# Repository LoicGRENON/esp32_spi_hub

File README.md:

SPI HUB for ESP32
=================
This repository contains the firmware source code and the hardware design
files.

The design is a fork of the ESP32 Brick from Tinkerforge : https://github.com/Tinkerforge/esp32-brick & https://www.tinkerforge.com/en/doc/Hardware/Bricks/ESP32_Brick.html

It is modified mainly to use "basic parts" components from JLCPCB for cost-effective assembly and also to use a ESP32 with external antenna (ESP32-WROOM-32UE-N16).

Hardware
--------

The hardware is designed with the open source EDA Suite KiCad 6.0 (http://www.kicad.org) and Kikit (https://github.com/yaqwsx/KiKit) is used to generate the assembly files.

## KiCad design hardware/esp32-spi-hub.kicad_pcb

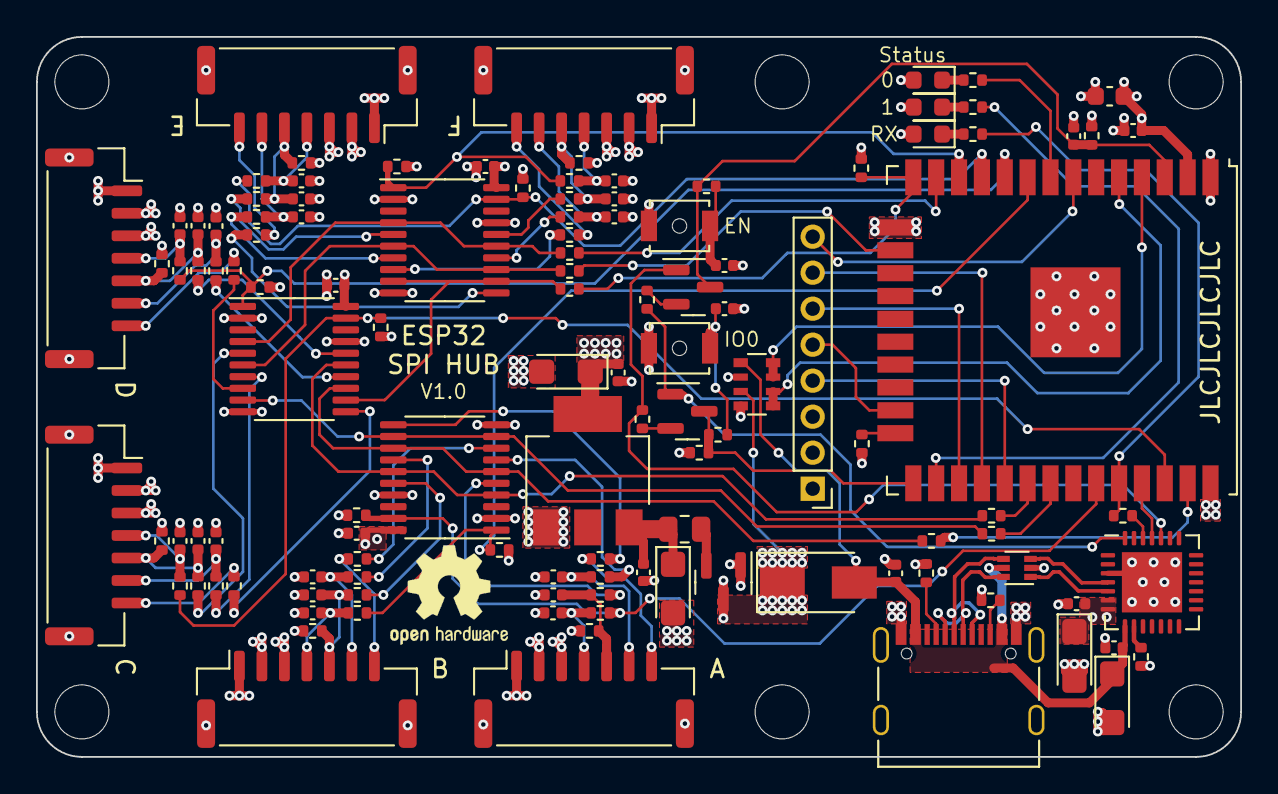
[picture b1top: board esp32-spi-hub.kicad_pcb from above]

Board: 4 copper layers, 66.9 x 40.0 mm, 124 parts (0 on the bottom side), 97 nets.

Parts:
C1, C3, C5, C7, C10, C12, C15, C22, C29: 0.1uF; C_0402_1005Metric
C2, C4, C8, C11: 10uF; CP_EIA-3216-18_Kemet-A
C6: 22uF; C_0603_1608Metric
C9: 10uF; C_0402_1005Metric
C13, C14: 1nF; C_0402_1005Metric
C16, C17, C18, C19, C20, C21, C23, C24, C25, C26, C27, C28, C30, C31, C32, C33, C34, C35: 220pF; C_0402_1005Metric
D1: SS34; D_SMA
D2: YE; LED_0603_1608Metric
D3: GN; LED_0603_1608Metric
D4: BU; LED_0603_1608Metric
FB1: 100 @ 100MHz; R_0805_2012Metric
H1, H2, H3, H4, H5, H6: MountingHole; MountingHole_3mm
J1: EXT_HEADER; PinHeader_1x08_P2.00mm_Vertical
J2, J3, J4, J5, J6, J7: SM07B-GHS-TB; JST_GH_SM07B-GHS-TB_1x07-1MP_P1.25mm_Horizontal
P1: USB_C_Plug_USB2.0; USB_C_Receptacle_Palconn_UTC16-G
Q1: AO3401A; SOT-23
Q2, Q3: S8050; SOT-23
R1: 4.7k; R_0402_1005Metric
R2, R9, R10, R11, R12, R13, R14, R23, R24, R25, R26, R30, R31, R32, R33, R35, R36, R37, R38, R42, R43, R44, R45, R47, R48, R49, R50, R54, R55, R56, R57: 100; R_0402_1005Metric
R3, R4, R5, R6: 12k; R_0402_1005Metric
R7, R8: DNP; R_0402_1005Metric
R15, R16: 5.1k; R_0402_1005Metric
R17, R21: 470; R_0402_1005Metric
R18, R19, R20: 1k; R_0402_1005Metric
R22, R27, R34, R39, R46, R51: 100k; R_0402_1005Metric
R28, R29, R40, R41, R52, R53: 10k; R_0402_1005Metric
RN1: 1k; R_Array_Convex_4x0603
SW1, SW2: SW_Push; SW_SPST_B3U-1000P-B
U1: AMS1117-3.3; SOT-223-3_TabPin2
U2: CP2102-GMR; QFN-28-1EP_5x5mm_P0.5mm_EP3.35x3.35mm
U3: ESP32-WROOM-32UE-N16; ESP32-WROOM-32U
U4: 82400152; SOT-563
U5, U6, U7: 74HC244; TSSOP-20_4.4x6.5mm_P0.65mm

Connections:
5V_USB: C10.1, C11.1, C12.1, D1.2 (A), P1.A4 (VBUS), P1.A9 (VBUS), P1.B4 (VBUS), P1.B9 (VBUS), RN1.5 (R4.2), U2.8 (VBUS), U4.5 (VBUS)
+3V3: C3.1, C4.1, C5.1, C6.1, C7.1, C8.1, C15.1, C22.1, C29.1, D2.2 (A), D3.2 (A), D4.2 (A), J1.3, J2.3, J3.3, J4.3, J5.3, J6.3, J7.3, R1.1, R3.1, R6.1, R22.1, R27.1, R28.1, R29.1, R34.1, R39.1, R40.1, R41.1, R46.1, R51.1, R52.1, R53.1, U1.2 (VO), U2.6 (VDD), U2.7 (VREGIN), U3.2 (VDD), U5.20 (VCC), U6.20 (VCC), U7.20 (VCC)
+5V: D1.1 (K), J1.1, J2.1, J3.1, J4.1, J5.1, J6.1, J7.1, Q1.3 (D), RN1.7 (R2.2)
/IO12: R8.1, R9.1, U3.14 (IO12)
/IO13: R10.1, U3.16 (IO13)
/IO14: R11.1, U3.13 (IO14)
/IO18: R12.1, U3.30 (IO18)
/IO19: R13.1, U3.31 (IO19)
/IO23: R14.1, U3.37 (IO23)
/SPI ports A & B/S1_CLK: R24.1, U5.16 (1Y1)
/SPI ports A & B/S1_MISO: R26.1, U5.8 (1A3)
/SPI ports A & B/S1_MOSI: R25.1, U5.14 (1Y2)
/SPI ports A & B/S2_CLK: R31.1, U5.5 (2Y1)
/SPI ports A & B/S2_MISO: R33.1, U5.11 (2A3)
/SPI ports A & B/S2_MOSI: R32.1, U5.7 (2Y2)
/SPI ports C & D/S1_CLK: R36.1, U6.16 (1Y1)
/SPI ports C & D/S1_MISO: R38.1, U6.8 (1A3)
/SPI ports C & D/S1_MOSI: R37.1, U6.14 (1Y2)
/SPI ports C & D/S2_CLK: R43.1, U6.5 (2Y1)
/SPI ports C & D/S2_MISO: R45.1, U6.11 (2A3)
/SPI ports C & D/S2_MOSI: R44.1, U6.7 (2Y2)
/SPI ports E & F/S1_CLK: R48.1, U7.16 (1Y1)
/SPI ports E & F/S1_MISO: R50.1, U7.8 (1A3)
/SPI ports E & F/S1_MOSI: R49.1, U7.14 (1Y2)
/SPI ports E & F/S2_CLK: R55.1, U7.5 (2Y1)
/SPI ports E & F/S2_MISO: R57.1, U7.11 (2A3)
/SPI ports E & F/S2_MOSI: R56.1, U7.7 (2Y2)
B0-CLK: R11.2, U6.4 (1A1), U7.4 (1A1), U7.15 (2A1)
B0-MISO: R9.2, U6.12 (1Y3), U7.9 (2Y3), U7.12 (1Y3)
B0-MOSI: R10.2, U6.6 (1A2), U7.6 (1A2), U7.13 (2A2)
B0_CS0: R47.1, R53.2, U3.12 (IO27), U7.1 (1OE)
B0_CS1: R52.2, R54.1, U3.11 (IO26), U7.19 (2OE)
B0_CS2: R35.1, R41.2, U3.10 (IO25), U6.1 (1OE)
B1-CLK: R12.2, U5.4 (1A1), U5.15 (2A1), U6.15 (2A1)
B1-MISO: R13.2, U5.9 (2Y3), U5.12 (1Y3), U6.9 (2Y3)
B1-MOSI: R14.2, U5.6 (1A2), U5.13 (2A2), U6.13 (2A2)
B1_CS0: R40.2, R42.1, U3.36 (IO22), U6.19 (2OE)
B1_CS1: R23.1, R29.2, U3.9 (IO33), U5.1 (1OE)
B1_CS2: R28.2, R30.1, U3.33 (IO21), U5.19 (2OE)
ESP_EN: C9.1, Q2.3 (C), R3.2, R17.2, U3.3 (EN)
ESP_IO0: Q3.3 (C), R6.2, R21.2, U3.25 (IO0)
ESP_IO2: R7.1, U3.24 (IO2)
ESP_IO5: J1.4, U3.29 (IO5)
ESP_IO15: J1.5, U3.23 (IO15)
ESP_IO16: J1.6, U3.27 (IO16)
ESP_IO17: J1.7, U3.28 (IO17)
ESP_IO35: J1.8, U3.7 (IO35)
ESP_RXD: R2.2, R18.2, U3.34 (RXD0/IO3)
ESP_TXD: U2.25 (RXD), U3.35 (TXD0/IO1)
GND: C1.2, C2.2, C3.2, C4.2, C5.2, C6.2, C7.2, C8.2, C9.2, C10.2, C11.2, C12.2, C13.2, C14.2, C15.2, C16.2, C17.2, C18.2, C19.2, C20.2, C21.2, C22.2, C23.2, C24.2, C25.2, C26.2, C27.2, C28.2, C29.2, C30.2, C31.2, C32.2, C33.2, C34.2, C35.2, J1.2, J2.2, J2.MP (MountPin), J3.2, J3.MP (MountPin), J4.2, J4.MP (MountPin), J5.2, J5.MP (MountPin), J6.2, J6.MP (MountPin), J7.2, J7.MP (MountPin), P1.A1 (GND), P1.A12 (GND), P1.B1 (GND), P1.B12 (GND), Q1.1 (G), R7.2, R8.2, R15.2, R16.2, RN1.6 (R3.2), RN1.8 (R1.2), SW1.1, SW2.1, U1.1 (GND), U2.3 (GND), U2.29 (GND), U3.1 (GND), U3.15 (GND), U3.38 (GND), U3.39 (GND), U4.2 (GND), U5.2 (1A0), U5.10 (GND), U5.17 (2A0), U6.2 (1A0), U6.10 (GND), U6.17 (2A0), U7.2 (1A0), U7.10 (GND), U7.17 (2A0)
LED_BLUE: R20.2, U3.8 (IO32)
LED_GREEN: R19.2, U3.26 (IO4)
unnamed: C1.1, C2.1, FB1.2, U1.3 (VI)
unnamed: C13.1, R17.1, SW1.2
unnamed: C14.1, R21.1, SW2.2
unnamed: C16.1, J2.4, R23.2
unnamed: C17.1, J2.5, R22.2, R24.2
unnamed: C18.1, J2.6, R25.2
unnamed: C19.1, J3.4, R30.2
unnamed: C20.1, J3.5, R27.2, R31.2
unnamed: C21.1, J3.6, R32.2
unnamed: C23.1, J4.4, R35.2
unnamed: C24.1, J4.5, R34.2, R36.2
unnamed: C25.1, J4.6, R37.2
unnamed: C26.1, J5.4, R42.2
unnamed: C27.1, J5.5, R39.2, R43.2
unnamed: C28.1, J5.6, R44.2
unnamed: C30.1, J6.4, R47.2
unnamed: C31.1, J6.5, R46.2, R48.2
unnamed: C32.1, J6.6, R49.2
unnamed: C33.1, J7.4, R54.2
unnamed: C34.1, J7.5, R51.2, R55.2
unnamed: C35.1, J7.6, R56.2
unnamed: D2.1 (K), R18.1
unnamed: D3.1 (K), R19.1
unnamed: D4.1 (K), R20.1
unnamed: FB1.1, Q1.2 (S)
unnamed: J2.7, R26.2
unnamed: J3.7, R33.2
unnamed: J4.7, R38.2
unnamed: J5.7, R45.2
unnamed: J6.7, R50.2
unnamed: J7.7, R57.2
unnamed: P1.A5 (CC), R15.1
unnamed: P1.B5 (VCONN), R16.1
unnamed: Q2.1 (E), R5.1, U2.24 (~RTS)
unnamed: Q2.2 (B), R4.2
unnamed: Q3.1 (E), R4.1, U2.28 (~DTR)
unnamed: Q3.2 (B), R5.2
unnamed: R1.2, U2.9 (~RST)
unnamed: R2.1, U2.26 (TXD)
unnamed: RN1.1 (R1.1), RN1.2 (R2.1), U3.5 (SENSOR_VN)
unnamed: RN1.3 (R3.1), RN1.4 (R4.1), U3.4 (SENSOR_VP)
USB_CONN_D+: P1.A6 (D+), P1.B6 (D+), U4.4 (I/O2)
USB_CONN_D-: P1.A7 (D-), P1.B7 (D-), U4.6 (I/O1)
USB_D+: U2.4 (D+), U4.3 (I/O2)
USB_D-: U2.5 (D-), U4.1 (I/O1)

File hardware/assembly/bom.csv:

Comment,Designator,Footprint,LCSC
0.1uF,"C1,C3,C5,C7,C10,C12,C15,C22,C29",Capacitor_SMD:C_0402_1005Metric,C1525
10uF,"C2,C4,C8,C11",Capacitor_Tantalum_SMD:CP_EIA-3216-18_Kemet-A,C7171
22uF,C6,Capacitor_SMD:C_0603_1608Metric,C59461
10uF,C9,Capacitor_SMD:C_0402_1005Metric,C15525
1nF,"C13,C14",Capacitor_SMD:C_0402_1005Metric,C1523
220pF,"C16,C17,C18,C19,C20,C21,C23,C24,C25,C26,C27,C28,C30,C31,C32,C33,C34,C35",Capacitor_SMD:C_0402_1005Metric,C1530
SS34,D1,Diode_SMD:D_SMA,C8678
YE,D2,LED_SMD:LED_0603_1608Metric,C72038
GN,D3,LED_SMD:LED_0603_1608Metric,C72043
BU,D4,LED_SMD:LED_0603_1608Metric,C72041
100 @ 100MHz,FB1,Resistor_SMD:R_0805_2012Metric,C1015
EXT_HEADER,J1,Connector_PinHeader_2.00mm:PinHeader_1x08_P2.00mm_Vertical,-
SM07B-GHS-TB,"J2,J3,J4,J5,J6,J7",Connector_JST:JST_GH_SM07B-GHS-TB_1x07-1MP_P1.25mm_Horizontal,C495552
USB_C_Plug_USB2.0,P1,Connector_USB:USB_C_Receptacle_Palconn_UTC16-G,C709357
AO3401A,Q1,Package_TO_SOT_SMD:SOT-23,C15127
S8050,"Q2,Q3",Package_TO_SOT_SMD:SOT-23,C2146
4.7k,R1,Resistor_SMD:R_0402_1005Metric,C25900
100,"R2,R9,R10,R11,R12,R13,R14,R23,R24,R25,R26,R30,R31,R32,R33,R35,R36,R37,R38,R42,R43,R44,R45,R47,R48,R49,R50,R54,R55,R56,R57",Resistor_SMD:R_0402_1005Metric,C25076
12k,"R3,R4,R5,R6",Resistor_SMD:R_0402_1005Metric,C25752
DNP,"R7,R8",Resistor_SMD:R_0402_1005Metric,-
5.1k,"R15,R16",Resistor_SMD:R_0402_1005Metric,C25905
470,"R17,R21",Resistor_SMD:R_0402_1005Metric,C25117
1k,"R18,R19,R20",Resistor_SMD:R_0402_1005Metric,C11702
100k,"R22,R27,R34,R39,R46,R51",Resistor_SMD:R_0402_1005Metric,C25741
10k,"R28,R29,R40,R41,R52,R53",Resistor_SMD:R_0402_1005Metric,C25744
1k,RN1,Resistor_SMD:R_Array_Convex_4x0603,C20197
SW_Push,"SW1,SW2",Button_Switch_SMD:SW_SPST_B3U-1000P-B,-
AMS1117-3.3,U1,Package_TO_SOT_SMD:SOT-223-3_TabPin2,C6186
CP2102-GMR,U2,Package_DFN_QFN:QFN-28-1EP_5x5mm_P0.5mm_EP3.35x3.35mm,C6568
ESP32-WROOM-32UE-N16,U3,RF_Module:ESP32-WROOM-32U,-
82400152,U4,Package_TO_SOT_SMD:SOT-563,-
74HC244,"U5,U6,U7",Package_SO:TSSOP-20_4.4x6.5mm_P0.65mm,C6835

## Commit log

2022-07-05 Add Readme
2022-07-05 Add PDF schematics
2022-07-05 Add JLCJLCJLCJLC on silkscreen for part number removal
